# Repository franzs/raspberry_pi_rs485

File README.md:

# RS485 shield for Raspberry Pi 2/3

This Raspberry Pi RS485 module was heavily inspired by an article
from the excellent german c't magazin:

[Unter Strom - Stromverbrauch analysieren mit Raspi und Smart Meter](https://www.heise.de/ct/ausgabe/2017-17-Stromverbrauch-analysieren-mit-Raspi-und-Smart-Meter-3787264.html)

In addition to the schematic published a level shifter was added
for the RXD input.

This shield was build around the [MAX485 module](http://www.chinalctech.com/index.php?_m=mod_product&_a=view&p_id=811) from LC Electronics.

There is an
[AISLER project](https://aisler.net/franz/raspberry-pi-rs485-module/main-pcb)
if you like to order a PCB.

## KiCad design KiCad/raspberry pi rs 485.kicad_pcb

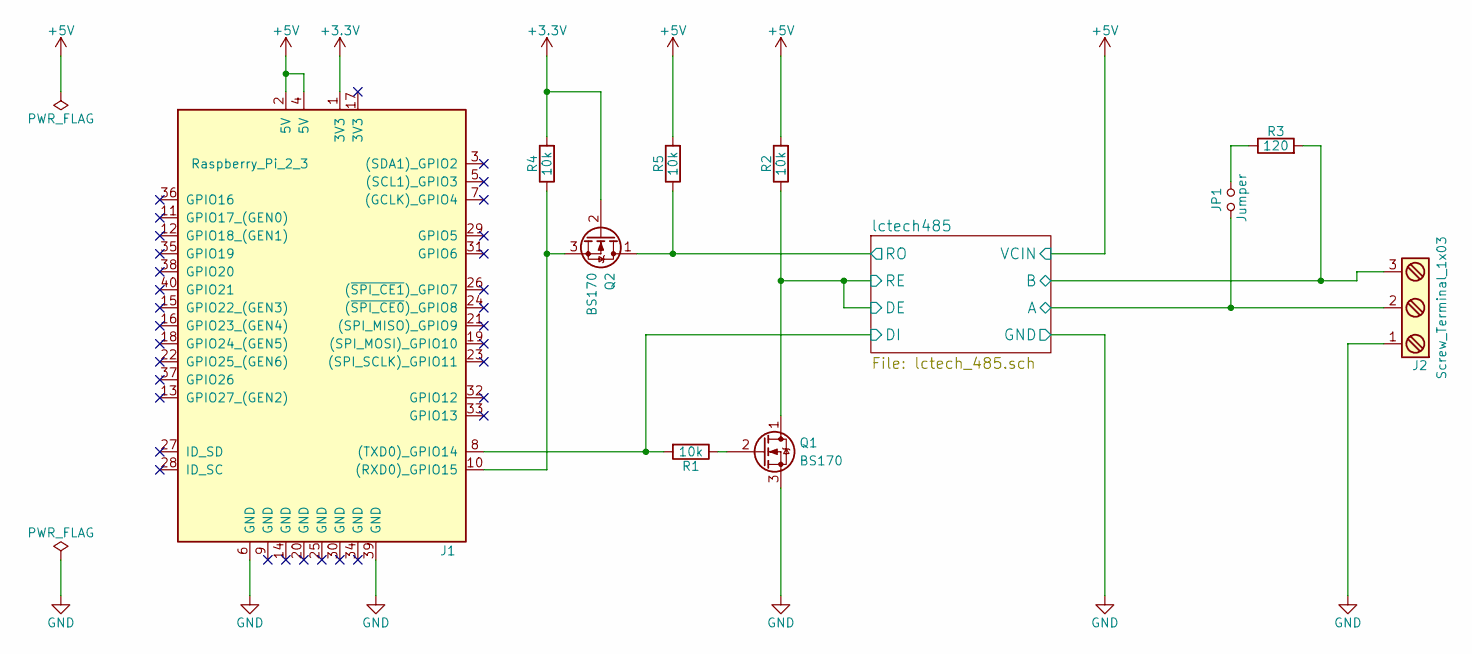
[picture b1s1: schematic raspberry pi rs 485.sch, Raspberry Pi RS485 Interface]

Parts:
J1: Raspberry_Pi_2_3; Pin_Header_Straight_2x20_Pitch2.54mm
J2: Screw_Terminal_1x03; bornier3
JP1: Jumper; Socket_Strip_Straight_2x01_Pitch2.54mm
Q1, Q2: BS170; TO-92_Molded_Wide_Oval
R1, R2, R4, R5: 10k; R_Axial_DIN0204_L3.6mm_D1.6mm_P7.62mm_Horizontal
R3: 120; R_Axial_DIN0204_L3.6mm_D1.6mm_P7.62mm_Horizontal

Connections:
+3V3: J1.1 (3V3), Q2.2 (G), R4.2
+5V: J1.2 (5V), J1.4 (5V), R2.2, R5.2; also elsewhere on the board
/lctech485/A: J2.2, JP1.1; also elsewhere on the board
/lctech485/B: J2.3, R3.2; also elsewhere on the board
/lctech485/DE: Q1.1 (D), R2.1; also elsewhere on the board
/lctech485/DI: J1.8 ((TXD0)_GPIO14), R1.2; also elsewhere on the board
/lctech485/RO: Q2.1 (D), R5.1; also elsewhere on the board
GND: J1.6 (GND), J1.39 (GND), J2.1, Q1.3 (S); also elsewhere on the board
unnamed: J1.10 ((RXD0)_GPIO15), Q2.3 (S), R4.1
unnamed: JP1.2, R3.1
unnamed: Q1.2 (G), R1.1

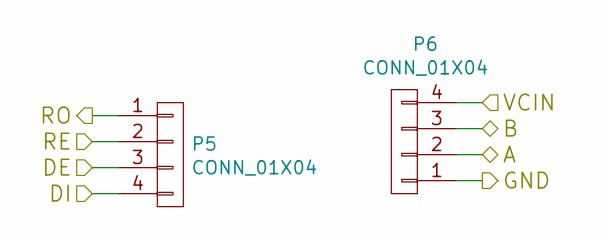
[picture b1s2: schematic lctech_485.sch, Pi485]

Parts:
P5, P6: CONN_01X04; Socket_Strip_Straight_1x04_Pitch2.54mm

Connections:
+5V: P6.4; also elsewhere on the board
/lctech485/A: P6.2; also elsewhere on the board
/lctech485/B: P6.3; also elsewhere on the board
/lctech485/DE: P5.2, P5.3; also elsewhere on the board
/lctech485/DI: P5.4; also elsewhere on the board
/lctech485/RO: P5.1; also elsewhere on the board
GND: P6.1; also elsewhere on the board

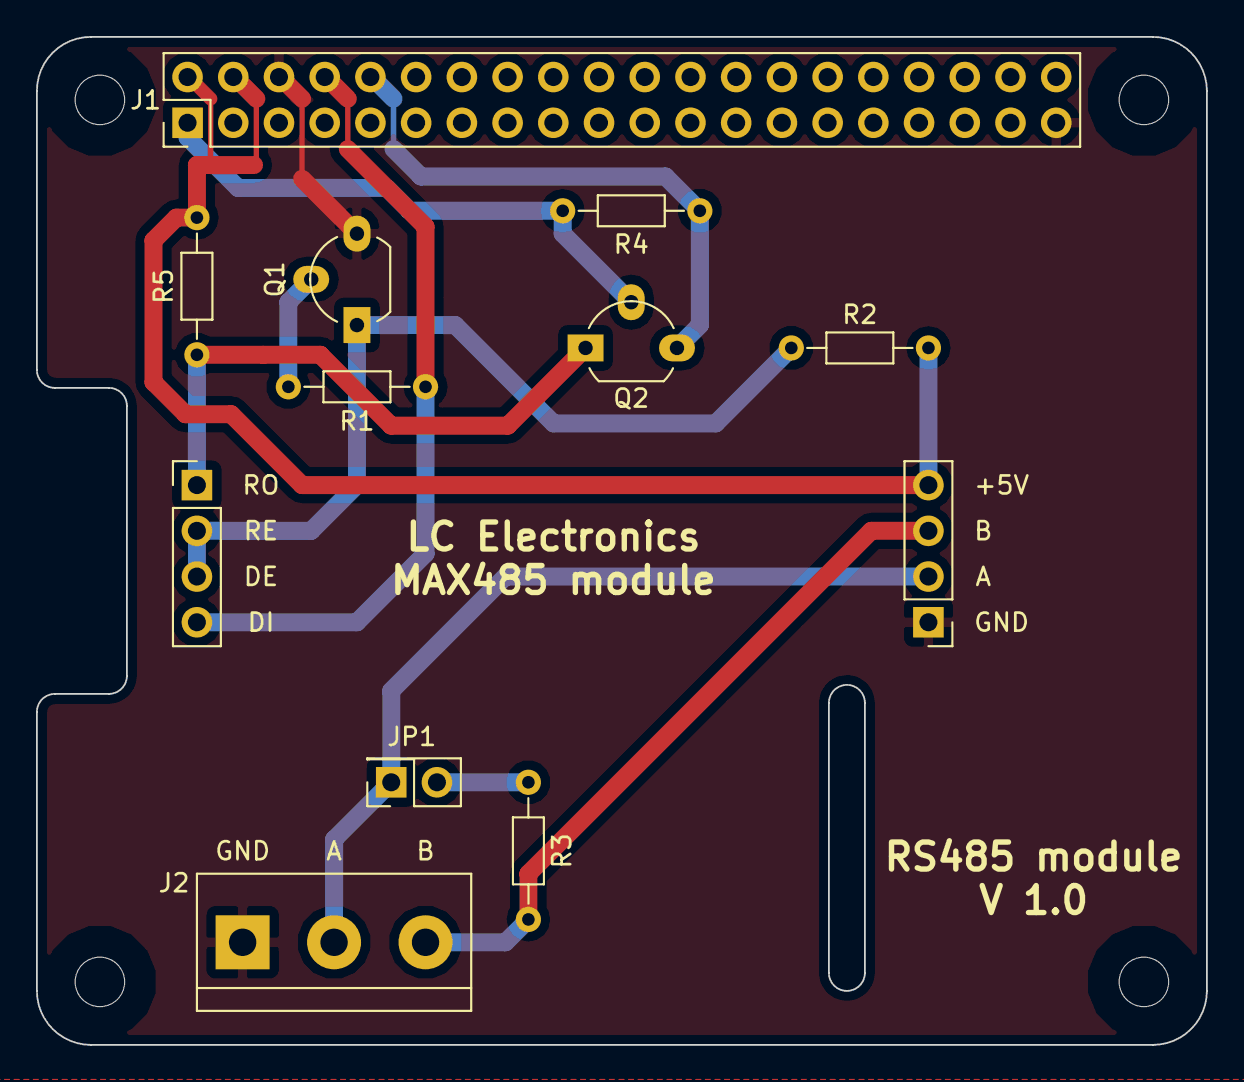
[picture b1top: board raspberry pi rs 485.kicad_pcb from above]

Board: 2 copper layers, 65.0 x 56.0 mm, 12 parts (0 on the bottom side), 11 nets.

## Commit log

2017-09-19 Add KiCad files.
2017-09-19 Add basic README.md
2017-09-19 Add link to MAX485 module from LC Electronics.
2017-09-19 Add PDF of schematic.
